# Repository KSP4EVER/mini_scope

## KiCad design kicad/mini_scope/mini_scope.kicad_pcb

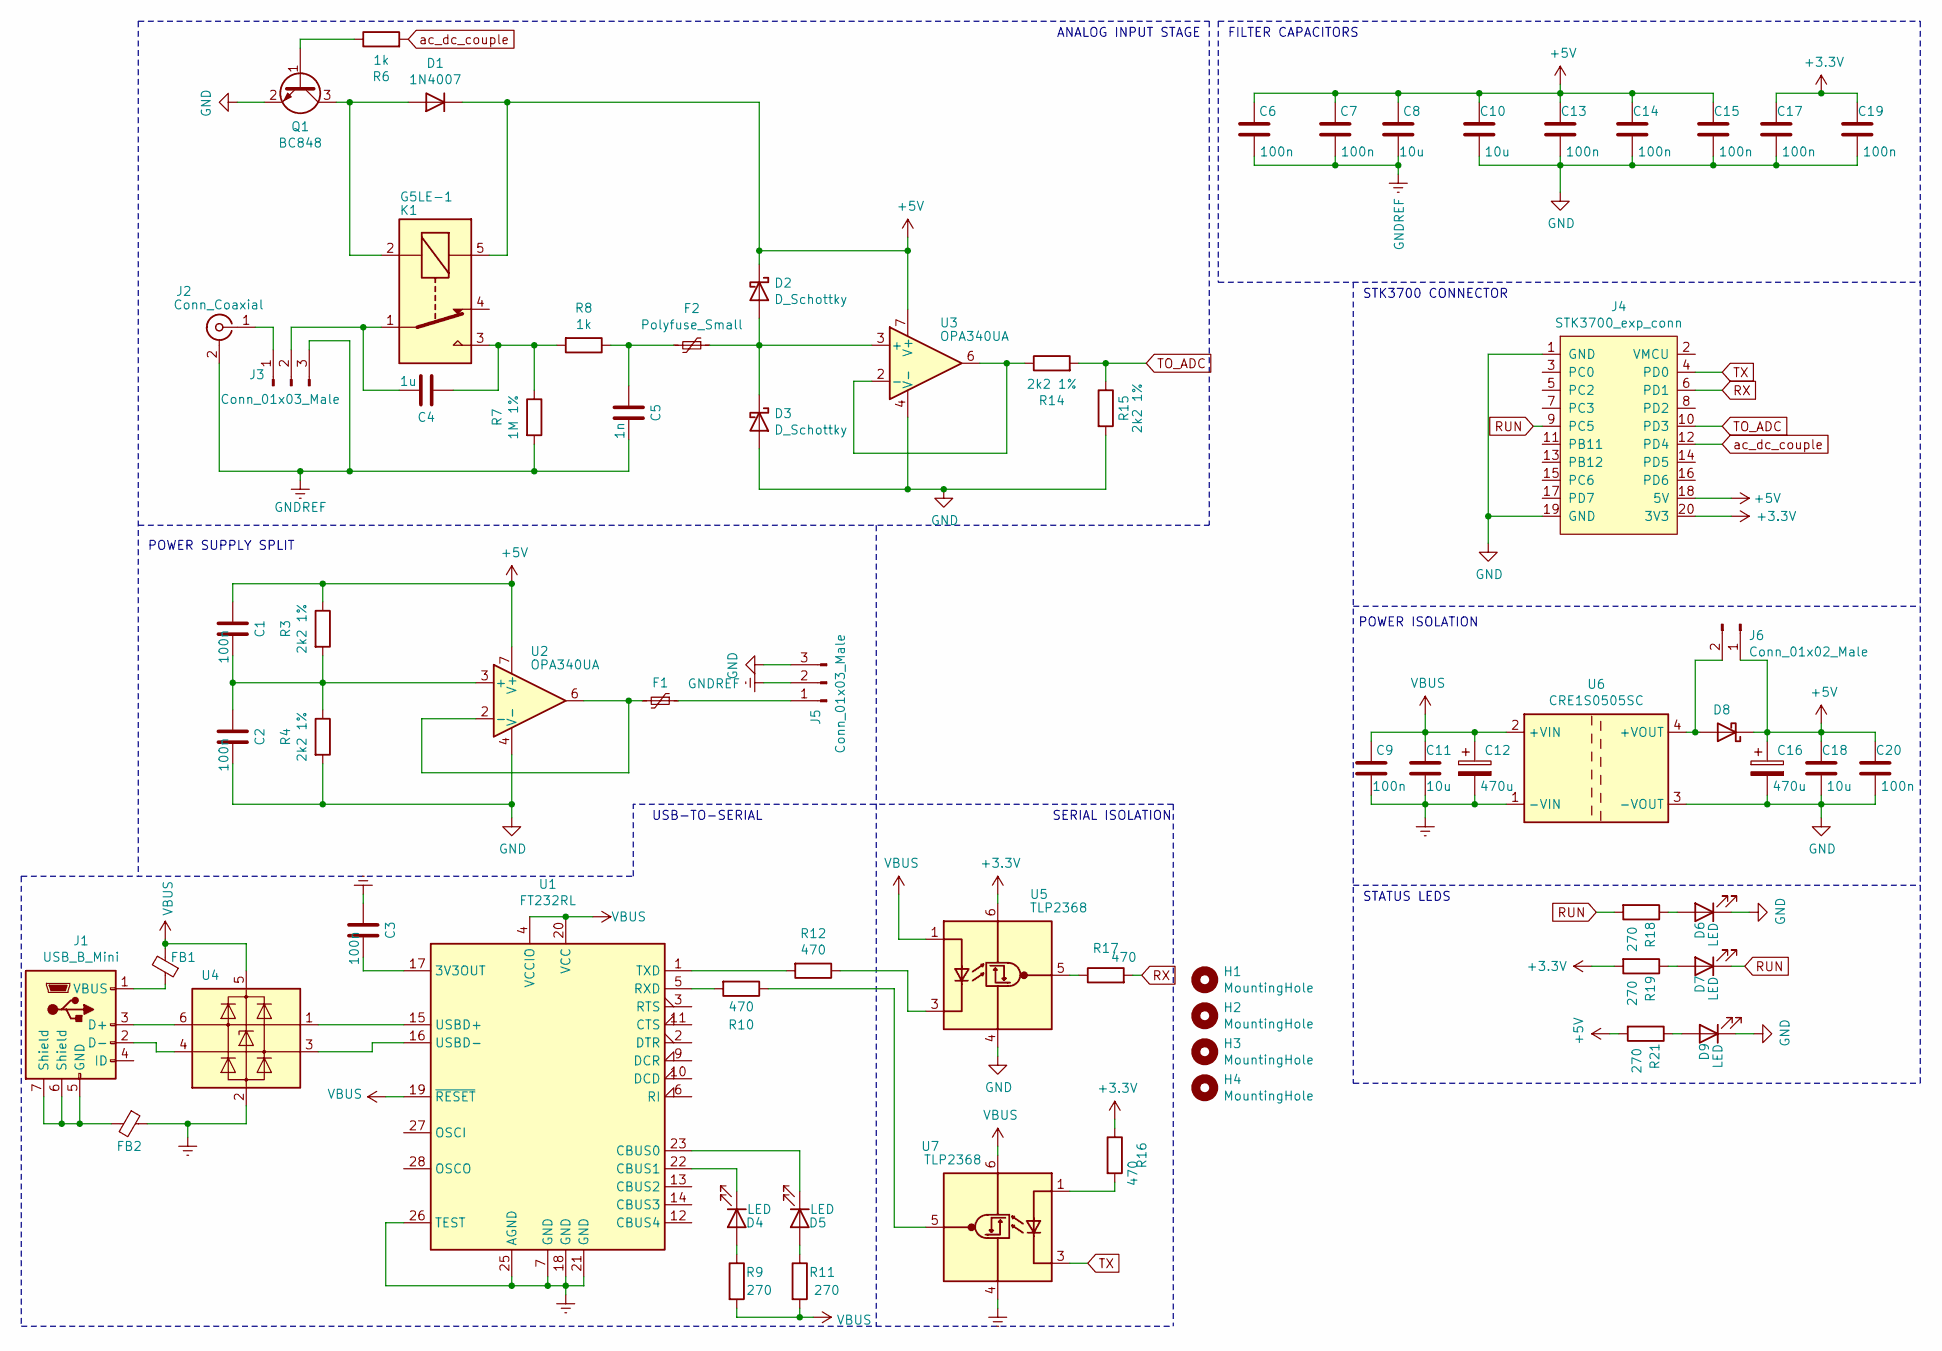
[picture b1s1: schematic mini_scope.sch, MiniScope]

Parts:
C1, C2, C3, C6, C7, C9, C13, C14, C15, C17, C19, C20: 100n; C_0805_2012Metric_Pad1.18x1.45mm_HandSolder
C4: 1u; C_0805_2012Metric_Pad1.18x1.45mm_HandSolder
C5: 1n; C_0805_2012Metric_Pad1.18x1.45mm_HandSolder
C8, C10, C11, C18: 10u; C_1210_3225Metric_Pad1.33x2.70mm_HandSolder
C12, C16: 470u; CP_Elec_8x10.5
D1: 1N4007; D_DO-41_SOD81_P10.16mm_Horizontal
D2, D3: D_Schottky; D_MicroMELF_Handsoldering
D4, D5, D6, D7, D9: LED; LED_0805_2012Metric_Pad1.15x1.40mm_HandSolder
D8: D_Schottky; D_SMA
F1, F2: Polyfuse_Small; R_1206_3216Metric_Pad1.30x1.75mm_HandSolder
FB1, FB2: Ferrite_Bead_Small; R_0805_2012Metric_Pad1.20x1.40mm_HandSolder
H1, H2, H3, H4: MountingHole; MountingHole_3.2mm_M3_DIN965_Pad
J1: USB_B_Mini; usb_b_mini
J2: Conn_Coaxial; BNC_Amphenol_B6252HB-NPP3G-50_Horizontal
J3, J5: Conn_01x03_Male; PinHeader_1x03_P2.54mm_Vertical
J4: STK3700_exp_conn; PinSocket_2x10_P2.54mm_Horizontal
J6: Conn_01x02_Male; PinHeader_1x02_P2.54mm_Vertical
K1: G5LE-1; Relay_SPDT_Omron-G5LE-1
Q1: BC848; SOT-23
R3, R4, R14, R15: 2k2 1%; R_0805_2012Metric_Pad1.20x1.40mm_HandSolder
R6, R8: 1k; R_0805_2012Metric_Pad1.20x1.40mm_HandSolder
R7: 1M 1%; R_0805_2012Metric_Pad1.20x1.40mm_HandSolder
R9, R11, R18, R19, R21: 270; R_0805_2012Metric_Pad1.20x1.40mm_HandSolder
R10, R12, R16, R17: 470; R_0805_2012Metric_Pad1.20x1.40mm_HandSolder
U1: FT232RL; SSOP-28_5.3x10.2mm_P0.65mm
U2, U3: OPA340UA; SOIC-8_3.9x4.9mm_P1.27mm
U4: USBLC6-2SC6; SOT-23-6
U5, U7: TLP2368; SO-5_4.4x3.6mm_P1.27mm
U6: CRE1S0505SC; Converter_DCDC_muRata_CRE1xxxxxxSC_THT

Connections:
+3V3: C17.1, C19.1, J4.20 (3V3), R16.1, R19.2, U5.6 (VDD)
+5V: C1.1, C6.1, C7.1, C8.1, C10.1, C13.1, C14.1, C15.1, C16.1, C18.1, C20.1, D1.1 (K), D2.1 (K), D8.1 (K), J4.18 (5V), J6.1, K1.5, R3.1, R21.2, U2.7 (V+), U3.7 (V+)
Earth: C3.1, C9.2, C11.2, C12.2, FB2.1, U1.7 (GND), U1.18 (GND), U1.21 (GND), U1.25 (AGND), U1.26 (TEST), U4.2 (GND), U6.1 (-VIN), U7.4 (GND)
GND: C2.2, C10.2, C13.2, C14.2, C15.2, C16.2, C17.2, C18.2, C19.2, C20.2, D3.2 (A), D6.1 (K), D9.1 (K), J4.1 (GND), J4.19 (GND), J5.3, Q1.2 (E), R4.2, R15.2, U2.4 (V-), U3.4 (V-), U5.4 (GND), U6.3 (-VOUT)
GNDREF: C5.2, C6.2, C7.2, C8.2, J2.2 (Ext), J3.3, J5.2, R7.2
unnamed: C1.2, C2.1, R3.2, R4.1, U2.3 (+)
unnamed: C3.2, U1.17 (3V3OUT)
unnamed: C4.1, K1.3, R7.1, R8.2
unnamed: C4.2, J3.2, K1.1
unnamed: C5.1, F2.2, R8.1
unnamed: D1.2 (A), K1.2, Q1.3 (C)
unnamed: D2.2 (A), D3.1 (K), F2.1, U3.3 (+)
unnamed: D4.1 (K), U1.22 (CBUS1)
unnamed: D4.2 (A), R9.1
unnamed: D5.1 (K), U1.23 (CBUS0)
unnamed: D5.2 (A), R11.1
unnamed: D6.2 (A), R18.1
unnamed: D7.2 (A), R19.1
unnamed: D8.2 (A), J6.2, U6.4 (+VOUT)
unnamed: D9.2 (A), R21.1
unnamed: F1.1, J5.1
unnamed: F1.2, U2.2 (-), U2.6
unnamed: FB1.1, J1.1 (VBUS)
unnamed: FB2.2, J1.5 (GND), J1.6 (Shield), J1.7 (Shield)
unnamed: J1.2 (D-), U4.4 (I/O2)
unnamed: J1.3 (D+), U4.6 (I/O1)
unnamed: J2.1 (In), J3.1
unnamed: Q1.1 (B), R6.1
unnamed: R10.1, U7.5 (VO)
unnamed: R10.2, U1.5 (RXD)
unnamed: R12.1, U5.3 (K)
unnamed: R12.2, U1.1 (TXD)
unnamed: R14.1, U3.2 (-), U3.6
unnamed: R16.2, U7.1 (A)
unnamed: R17.1, U5.5 (VO)
unnamed: U1.15 (USBD+), U4.1 (I/O1)
unnamed: U1.16 (USBD-), U4.3 (I/O2)
RUN: D7.1 (K), J4.9 (PC5), R18.2
RX: J4.6 (PD1), R17.2
TO_ADC: J4.10 (PD3), R14.2, R15.1
TX: J4.4 (PD0), U7.3 (K)
VBUS: C9.1, C11.1, C12.1, FB1.2, R9.2, R11.2, U1.4 (VCCIO), U1.19 (~RESET~), U1.20 (VCC), U4.5 (VBUS), U5.1 (A), U6.2 (+VIN), U7.6 (VDD)
ac_dc_couple: J4.12 (PD4), R6.2

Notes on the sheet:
USB-TO-SERIAL
SERIAL ISOLATION
POWER ISOLATION
POWER SUPPLY SPLIT
ANALOG INPUT STAGE
STK3700 CONNECTOR
FILTER CAPACITORS
STATUS LEDS

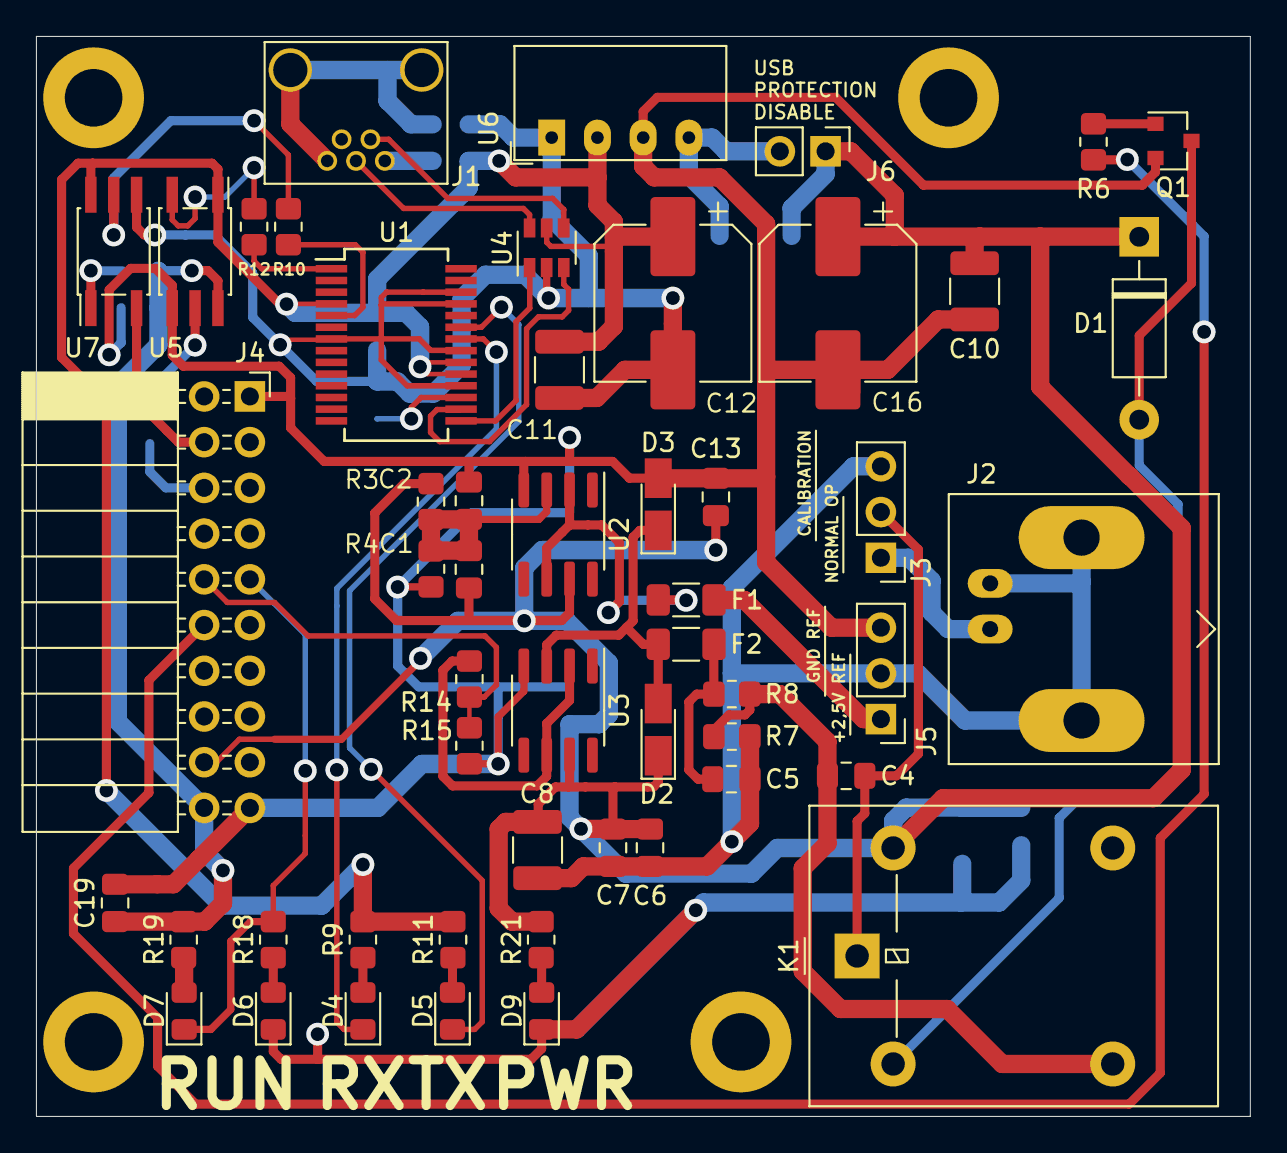
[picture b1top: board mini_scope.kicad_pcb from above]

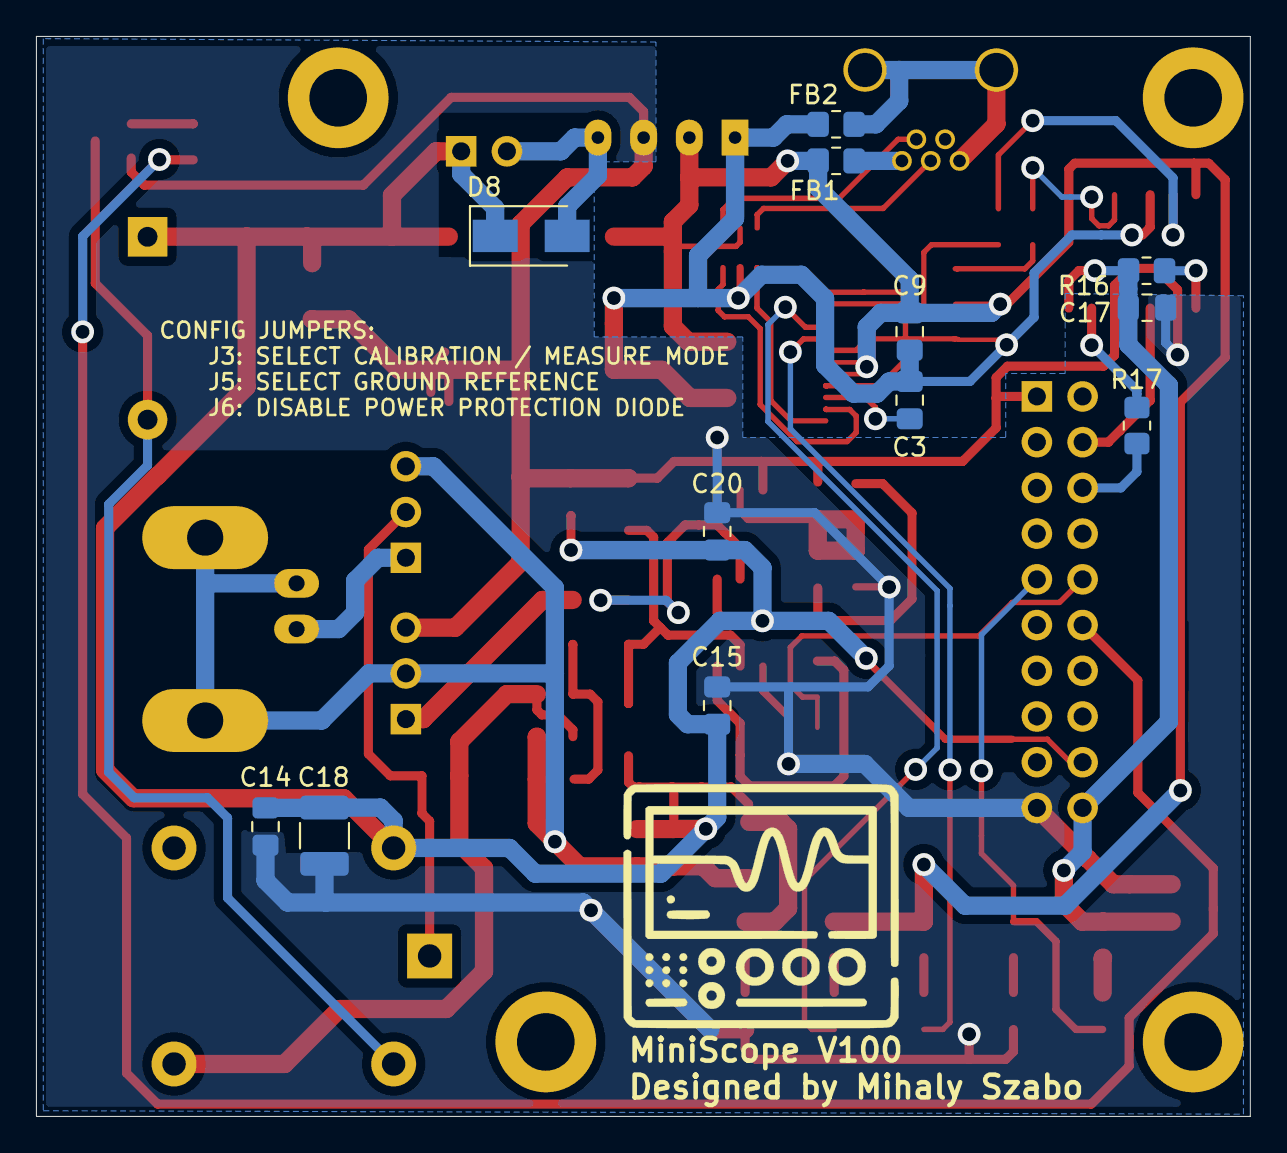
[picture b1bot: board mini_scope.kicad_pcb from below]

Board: 2 copper layers, 67.4 x 60.0 mm, 68 parts (12 on the bottom side), 43 nets.

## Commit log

2021-10-10 added tina sim, pc software: added cursor function
2021-10-10 added block diagram
2021-10-12 added icon
2021-10-13 created KiCad project, modified Tina simulation
2021-10-22 schematic complete
2021-11-05 almost finished pcb
2023-11-11 project refresh
